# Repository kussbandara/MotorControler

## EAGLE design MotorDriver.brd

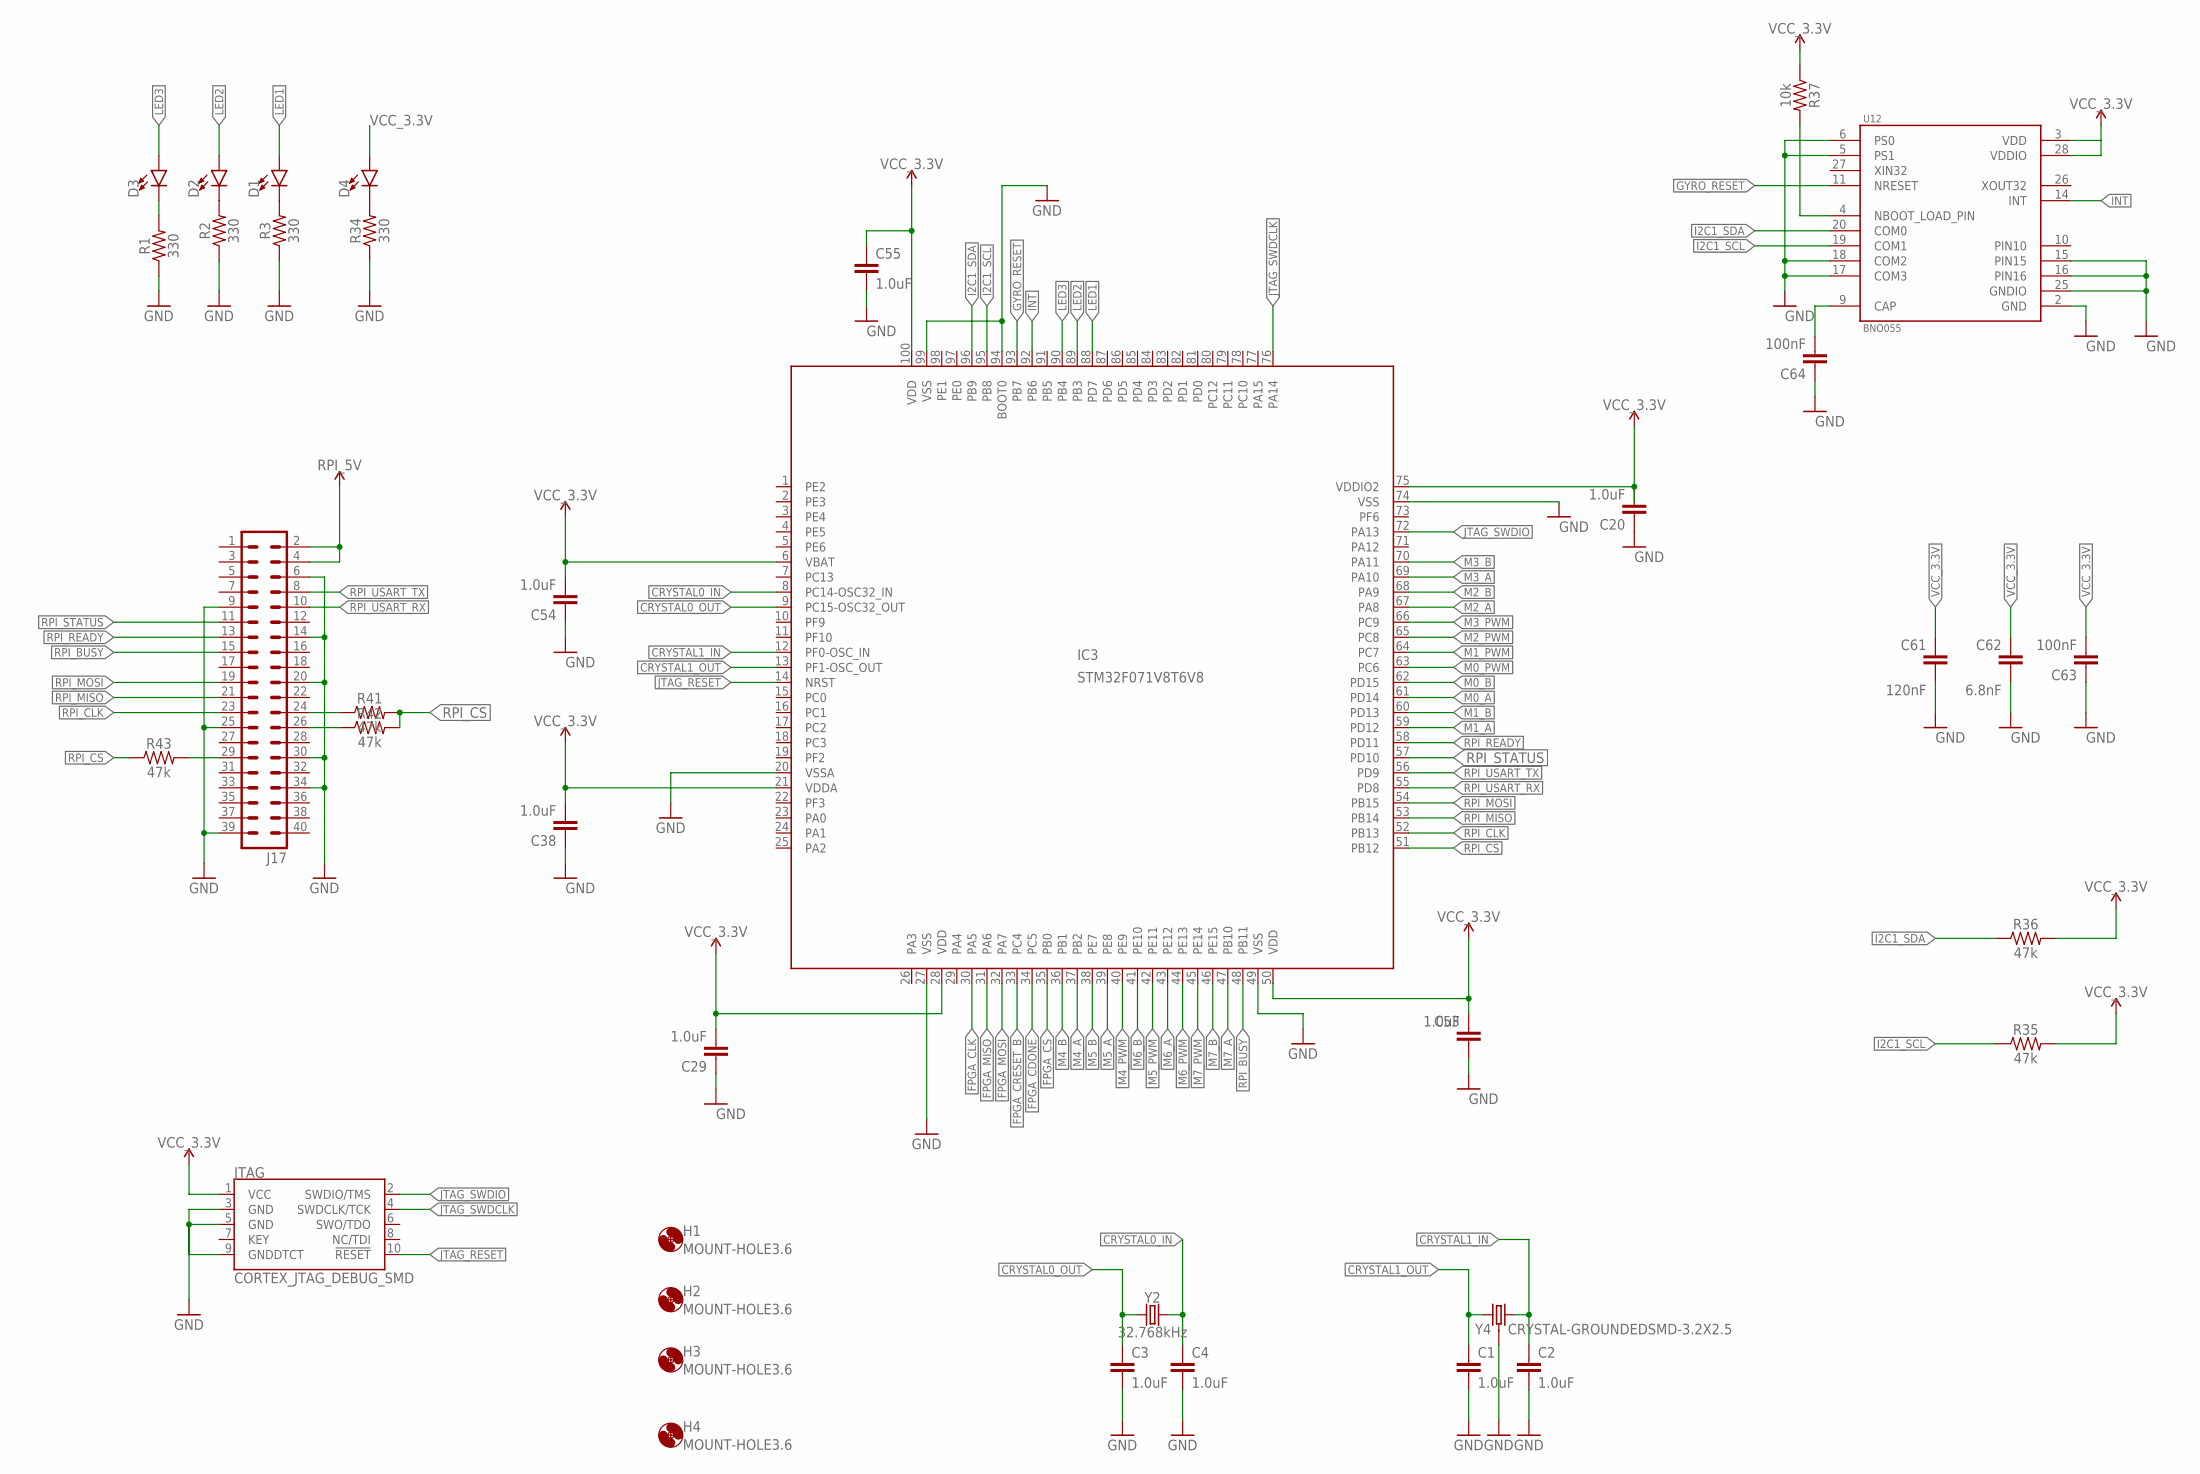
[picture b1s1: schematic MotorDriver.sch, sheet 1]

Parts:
C1, C2, C3, C4, C20, C29, C38, C53, C54, C55: 1.0uF; 0402-TIGHT
C61: 120nF; 0402-TIGHT
C62: 6.8nF; 0402-TIGHT
C63, C64: 100nF; 0402-TIGHT
D1, D2, D3, D4: LED0603; LED-0603
H1, H2, H3, H4: MOUNT-HOLE3.6; 3,6
IC3: STM32F071V8T6V8; LQFP100_14X14
J17: MA20-2
JTAG: CORTEX_JTAG_DEBUG_SMD; 2X5-SMD-1.27MM
R1, R2, R3, R34: 330; 0603
R35, R36, R41, R42, R43: 47k; 0402-TIGHT
R37: 10k; 0402-TIGHT
U12: BNO055; LGA28R50P4X10_380X520X100
Y2: 32.768kHz; CRYSTAL-SMD-3.2X1.5MM
Y4: CRYSTAL-GROUNDEDSMD-3.2X2.5; CRYSTAL-SMD-3.2X2.5MM

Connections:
CRYSTAL0_IN: C4.1, IC3.8 (PC14-OSC32_IN), Y2.P$2 (2)
CRYSTAL0_OUT: C3.1, IC3.9 (PC15-OSC32_OUT), Y2.P$1 (1)
CRYSTAL1_IN: C2.1, IC3.12 (PF0-OSC_IN), Y4.3 (2)
CRYSTAL1_OUT: C1.1, IC3.13 (PF1-OSC_OUT), Y4.1
FPGA_CDONE: IC3.34 (PC5); also elsewhere on the board
FPGA_CLK: IC3.30 (PA5); also elsewhere on the board
FPGA_CRESET_B: IC3.33 (PC4); also elsewhere on the board
FPGA_CS: IC3.35 (PB0); also elsewhere on the board
FPGA_MISO: IC3.31 (PA6); also elsewhere on the board
FPGA_MOSI: IC3.32 (PA7); also elsewhere on the board
GND: C1.2, C2.2, C3.2, C4.2, C20.1, C29.1, C38.1, C53.1, C54.1, C55.2, C61.1, C62.1, C63.1, C64.1, IC3.20 (VSSA), IC3.27 (VSS), IC3.49 (VSS), IC3.74 (VSS), IC3.94 (BOOT0), IC3.99 (VSS), J17.6, J17.9, J17.14, J17.20, J17.25, J17.30, J17.34, J17.39, JTAG.3 (GND), JTAG.5 (GND), JTAG.9 (GNDDTCT), R1.1, R2.1, R3.1, R34.1, U12.2 (GND), U12.5 (PS1), U12.6 (PS0), U12.15 (PIN15), U12.16 (PIN16), U12.17 (COM3), U12.18 (COM2), U12.25 (GNDIO), Y4.2 (3), Y4.4 (3); also elsewhere on the board
GYRO_RESET: IC3.93 (PB7), U12.11 (NRESET)
I2C1_SCL: IC3.95 (PB8), R35.1, U12.19 (COM1)
I2C1_SDA: IC3.96 (PB9), R36.1, U12.20 (COM0)
INT: IC3.92 (PB6), U12.14 (INT)
JTAG_RESET: IC3.14 (NRST), JTAG.10 (!RESET)
JTAG_SWDCLK: IC3.76 (PA14), JTAG.4 (SWDCLK/TCK)
JTAG_SWDIO: IC3.72 (PA13), JTAG.2 (SWDIO/TMS)
LED1: D1.A, IC3.88 (PD7)
LED2: D2.A, IC3.89 (PB3)
LED3: D3.A, IC3.90 (PB4)
M0_A: IC3.61 (PD14); also elsewhere on the board
M0_B: IC3.62 (PD15); also elsewhere on the board
M0_PWM: IC3.63 (PC6); also elsewhere on the board
M1_A: IC3.59 (PD12); also elsewhere on the board
M1_B: IC3.60 (PD13); also elsewhere on the board
M1_PWM: IC3.64 (PC7); also elsewhere on the board
M2_A: IC3.67 (PA8); also elsewhere on the board
M2_B: IC3.68 (PA9); also elsewhere on the board
M2_PWM: IC3.65 (PC8); also elsewhere on the board
M3_A: IC3.69 (PA10); also elsewhere on the board
M3_B: IC3.70 (PA11); also elsewhere on the board
M3_PWM: IC3.66 (PC9); also elsewhere on the board
M4_A: IC3.37 (PB2); also elsewhere on the board
M4_B: IC3.36 (PB1); also elsewhere on the board
M4_PWM: IC3.40 (PE9); also elsewhere on the board
M5_A: IC3.39 (PE8); also elsewhere on the board
M5_B: IC3.38 (PE7); also elsewhere on the board
M5_PWM: IC3.42 (PE11); also elsewhere on the board
M6_A: IC3.43 (PE12); also elsewhere on the board
M6_B: IC3.41 (PE10); also elsewhere on the board
M6_PWM: IC3.44 (PE13); also elsewhere on the board
M7_A: IC3.47 (PB10); also elsewhere on the board
M7_B: IC3.46 (PE15); also elsewhere on the board
M7_PWM: IC3.45 (PE14); also elsewhere on the board
unnamed: D3.C, R1.2
unnamed: D2.C, R2.2
unnamed: D1.C, R3.2
unnamed: D4.C, R34.2
unnamed: R37.2, U12.4 (NBOOT_LOAD_PIN)
unnamed: C64.2, U12.9 (CAP)
unnamed: J17.24, R41.1
unnamed: J17.26, R42.1
unnamed: J17.29, R43.2
PF3: IC3.22 (PF3)
PIN10: U12.10 (PIN10)
RPI_5V: J17.2, J17.4; also elsewhere on the board
RPI_BUSY: IC3.48 (PB11), J17.15
RPI_CLK: IC3.52 (PB13), J17.23
RPI_CS: IC3.51 (PB12), R41.2, R42.2, R43.1
RPI_MISO: IC3.53 (PB14), J17.21
RPI_MOSI: IC3.54 (PB15), J17.19
RPI_READY: IC3.58 (PD11), J17.13
RPI_STATUS: IC3.57 (PD10), J17.11
RPI_USART_RX: IC3.55 (PD8), J17.10
RPI_USART_TX: IC3.56 (PD9), J17.8
VCC_3.3V: C20.2, C29.2, C38.2, C53.2, C54.2, C55.1, C61.2, C62.2, C63.2, D4.A, IC3.6 (VBAT), IC3.21 (VDDA), IC3.28 (VDD), IC3.50 (VDD), IC3.75 (VDDIO2), IC3.100 (VDD), JTAG.1 (VCC), R35.2, R36.2, R37.1, U12.3 (VDD), U12.28 (VDDIO); also elsewhere on the board

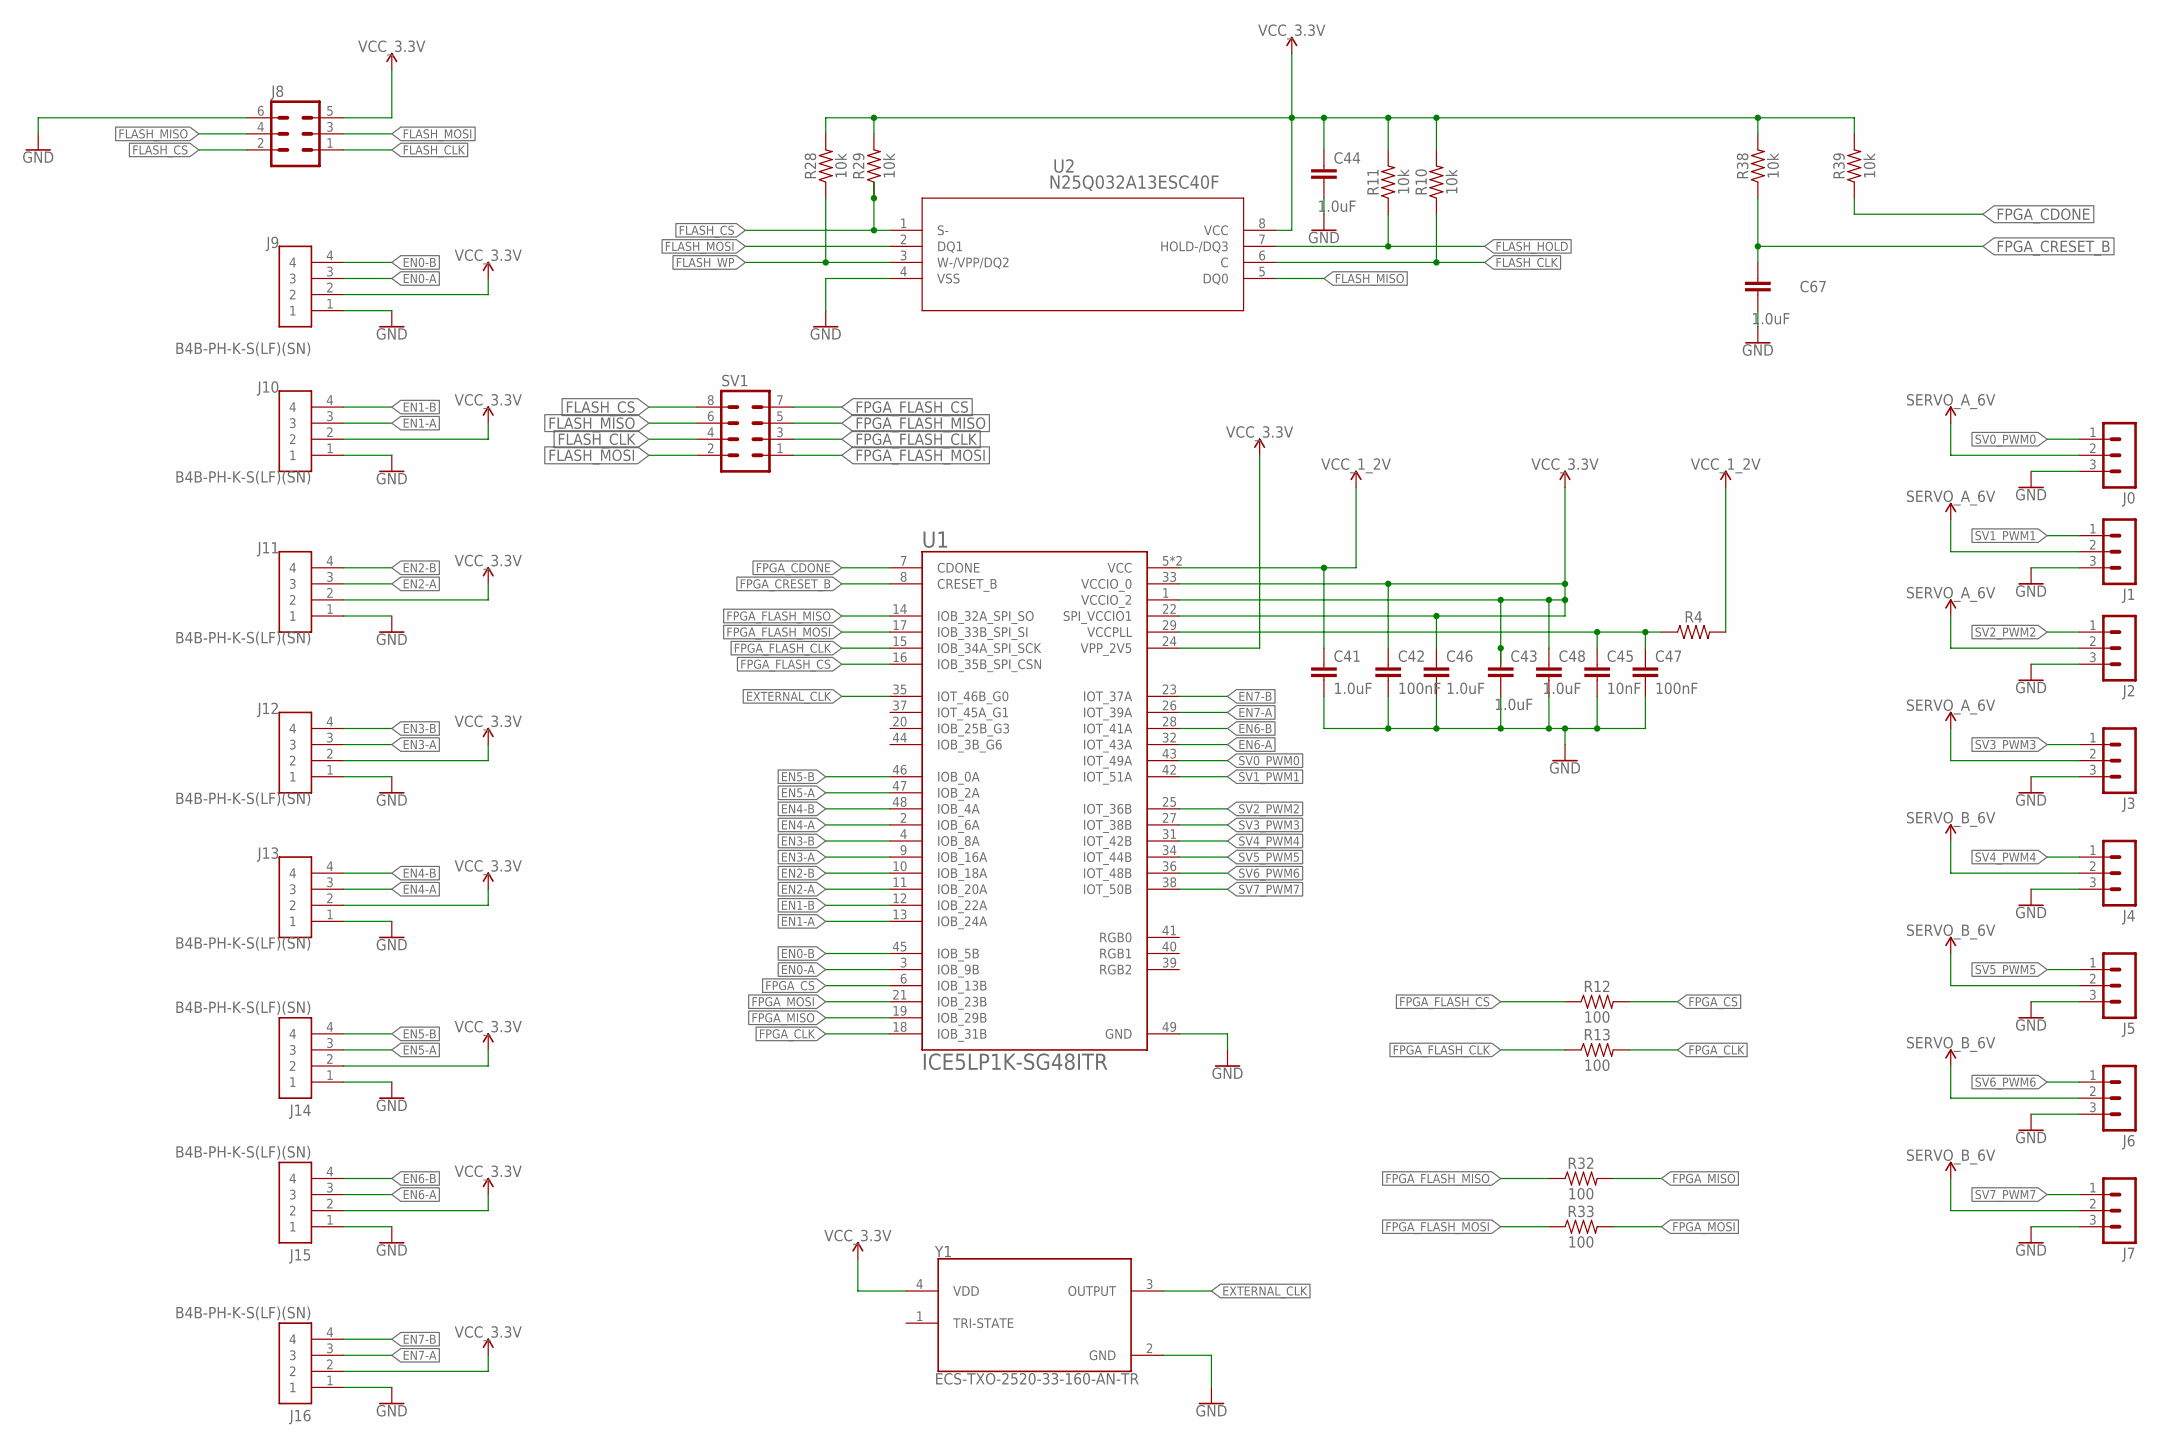
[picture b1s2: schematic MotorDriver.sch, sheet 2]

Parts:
C41, C43, C44, C46, C48, C67: 1.0uF; 0402-TIGHT
C42, C47: 100nF; 0402-TIGHT
C45: 10nF; 0402-TIGHT
J0, J1, J2, J3, J4, J5, J6, J7: MA03-1
J8: MA03-2
J9, J10, J11, J12, J13, J14, J15, J16: B4B-PH-K-S(LF)(SN); JST_B4B-PH-K-S(LF)(SN)
R4: 100; 0402-TIGHT
R10, R11, R28, R29, R38, R39: 10k; 0603
R12, R13, R32, R33: 100; 0603
SV1: MA04-2
U1: ICE5LP1K-SG48ITR; QFN50P700X700X100-49N
U2: N25Q032A13ESC40F; SO8N_5X4_MRN
Y1: ECS-TXO-2520-33-160-AN-TR; OSC_ECS-TXO-2520-33-160-AN-TR

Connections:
EN0-A: J9.3, U1.3 (IOB_9B)
EN0-B: J9.4, U1.45 (IOB_5B)
EN1-A: J10.3, U1.13 (IOB_24A)
EN1-B: J10.4, U1.12 (IOB_22A)
EN2-A: J11.3, U1.11 (IOB_20A)
EN2-B: J11.4, U1.10 (IOB_18A)
EN3-A: J12.3, U1.9 (IOB_16A)
EN3-B: J12.4, U1.4 (IOB_8A)
EN4-A: J13.3, U1.2 (IOB_6A)
EN4-B: J13.4, U1.48 (IOB_4A)
EN5-A: J14.3, U1.47 (IOB_2A)
EN5-B: J14.4, U1.46 (IOB_0A)
EN6-A: J15.3, U1.32 (IOT_43A)
EN6-B: J15.4, U1.28 (IOT_41A)
EN7-A: J16.3, U1.26 (IOT_39A)
EN7-B: J16.4, U1.23 (IOT_37A)
EXTERNAL_CLK: U1.35 (IOT_46B_G0), Y1.3 (OUTPUT)
FLASH_CLK: J8.1, R10.1, SV1.4, U2.6 (C)
FLASH_CS: J8.2, R29.1, SV1.8, U2.1 (S-)
FLASH_HOLD: R11.1, U2.7 (HOLD-/DQ3)
FLASH_MISO: J8.4, SV1.6, U2.5 (DQ0)
FLASH_MOSI: J8.3, SV1.2, U2.2 (DQ1)
FLASH_WP: R28.1, U2.3 (W-/VPP/DQ2)
FPGA_CDONE: R39.1, U1.7 (CDONE); also elsewhere on the board
FPGA_CLK: R13.2, U1.18 (IOB_31B); also elsewhere on the board
FPGA_CRESET_B: C67.1, R38.1, U1.8 (CRESET_B); also elsewhere on the board
FPGA_CS: R12.2, U1.6 (IOB_13B); also elsewhere on the board
FPGA_FLASH_CLK: R13.1, SV1.3, U1.15 (IOB_34A_SPI_SCK)
FPGA_FLASH_CS: R12.1, SV1.7, U1.16 (IOB_35B_SPI_CSN)
FPGA_FLASH_MISO: R32.1, SV1.5, U1.14 (IOB_32A_SPI_SO)
FPGA_FLASH_MOSI: R33.1, SV1.1, U1.17 (IOB_33B_SPI_SI)
FPGA_MISO: R32.2, U1.19 (IOB_29B); also elsewhere on the board
FPGA_MOSI: R33.2, U1.21 (IOB_23B); also elsewhere on the board
GND: C41.2, C42.2, C43.2, C44.2, C45.2, C46.2, C47.2, C48.2, C67.2, J0.3, J1.3, J2.3, J3.3, J4.3, J5.3, J6.3, J7.3, J8.6, J9.1, J10.1, J11.1, J12.1, J13.1, J14.1, J15.1, J16.1, U1.49 (GND), U2.4 (VSS), Y1.2 (GND); also elsewhere on the board
unnamed: C45.1, C47.1, R4.1, U1.29 (VCCPLL)
SERVO_A_6V: J0.2, J1.2, J2.2, J3.2; also elsewhere on the board
SERVO_B_6V: J4.2, J5.2, J6.2, J7.2; also elsewhere on the board
SV0_PWM0: J0.1, U1.43 (IOT_49A)
SV1_PWM1: J1.1, U1.42 (IOT_51A)
SV2_PWM2: J2.1, U1.25 (IOT_36B)
SV3_PWM3: J3.1, U1.27 (IOT_38B)
SV4_PWM4: J4.1, U1.31 (IOT_42B)
SV5_PWM5: J5.1, U1.34 (IOT_44B)
SV6_PWM6: J6.1, U1.36 (IOT_48B)
SV7_PWM7: J7.1, U1.38 (IOT_50B)
VCC_1_2V: C41.1, R4.2, U1.5 (VCC), U1.30 (VCC); also elsewhere on the board
VCC_3.3V: C42.1, C43.1, C44.1, C46.1, C48.1, J8.5, J9.2, J10.2, J11.2, J12.2, J13.2, J14.2, J15.2, J16.2, R10.2, R11.2, R28.2, R29.2, R38.2, R39.2, U1.1 (VCCIO_2), U1.22 (SPI_VCCIO1), U1.24 (VPP_2V5), U1.33 (VCCIO_0), U2.8 (VCC), Y1.4 (VDD); also elsewhere on the board

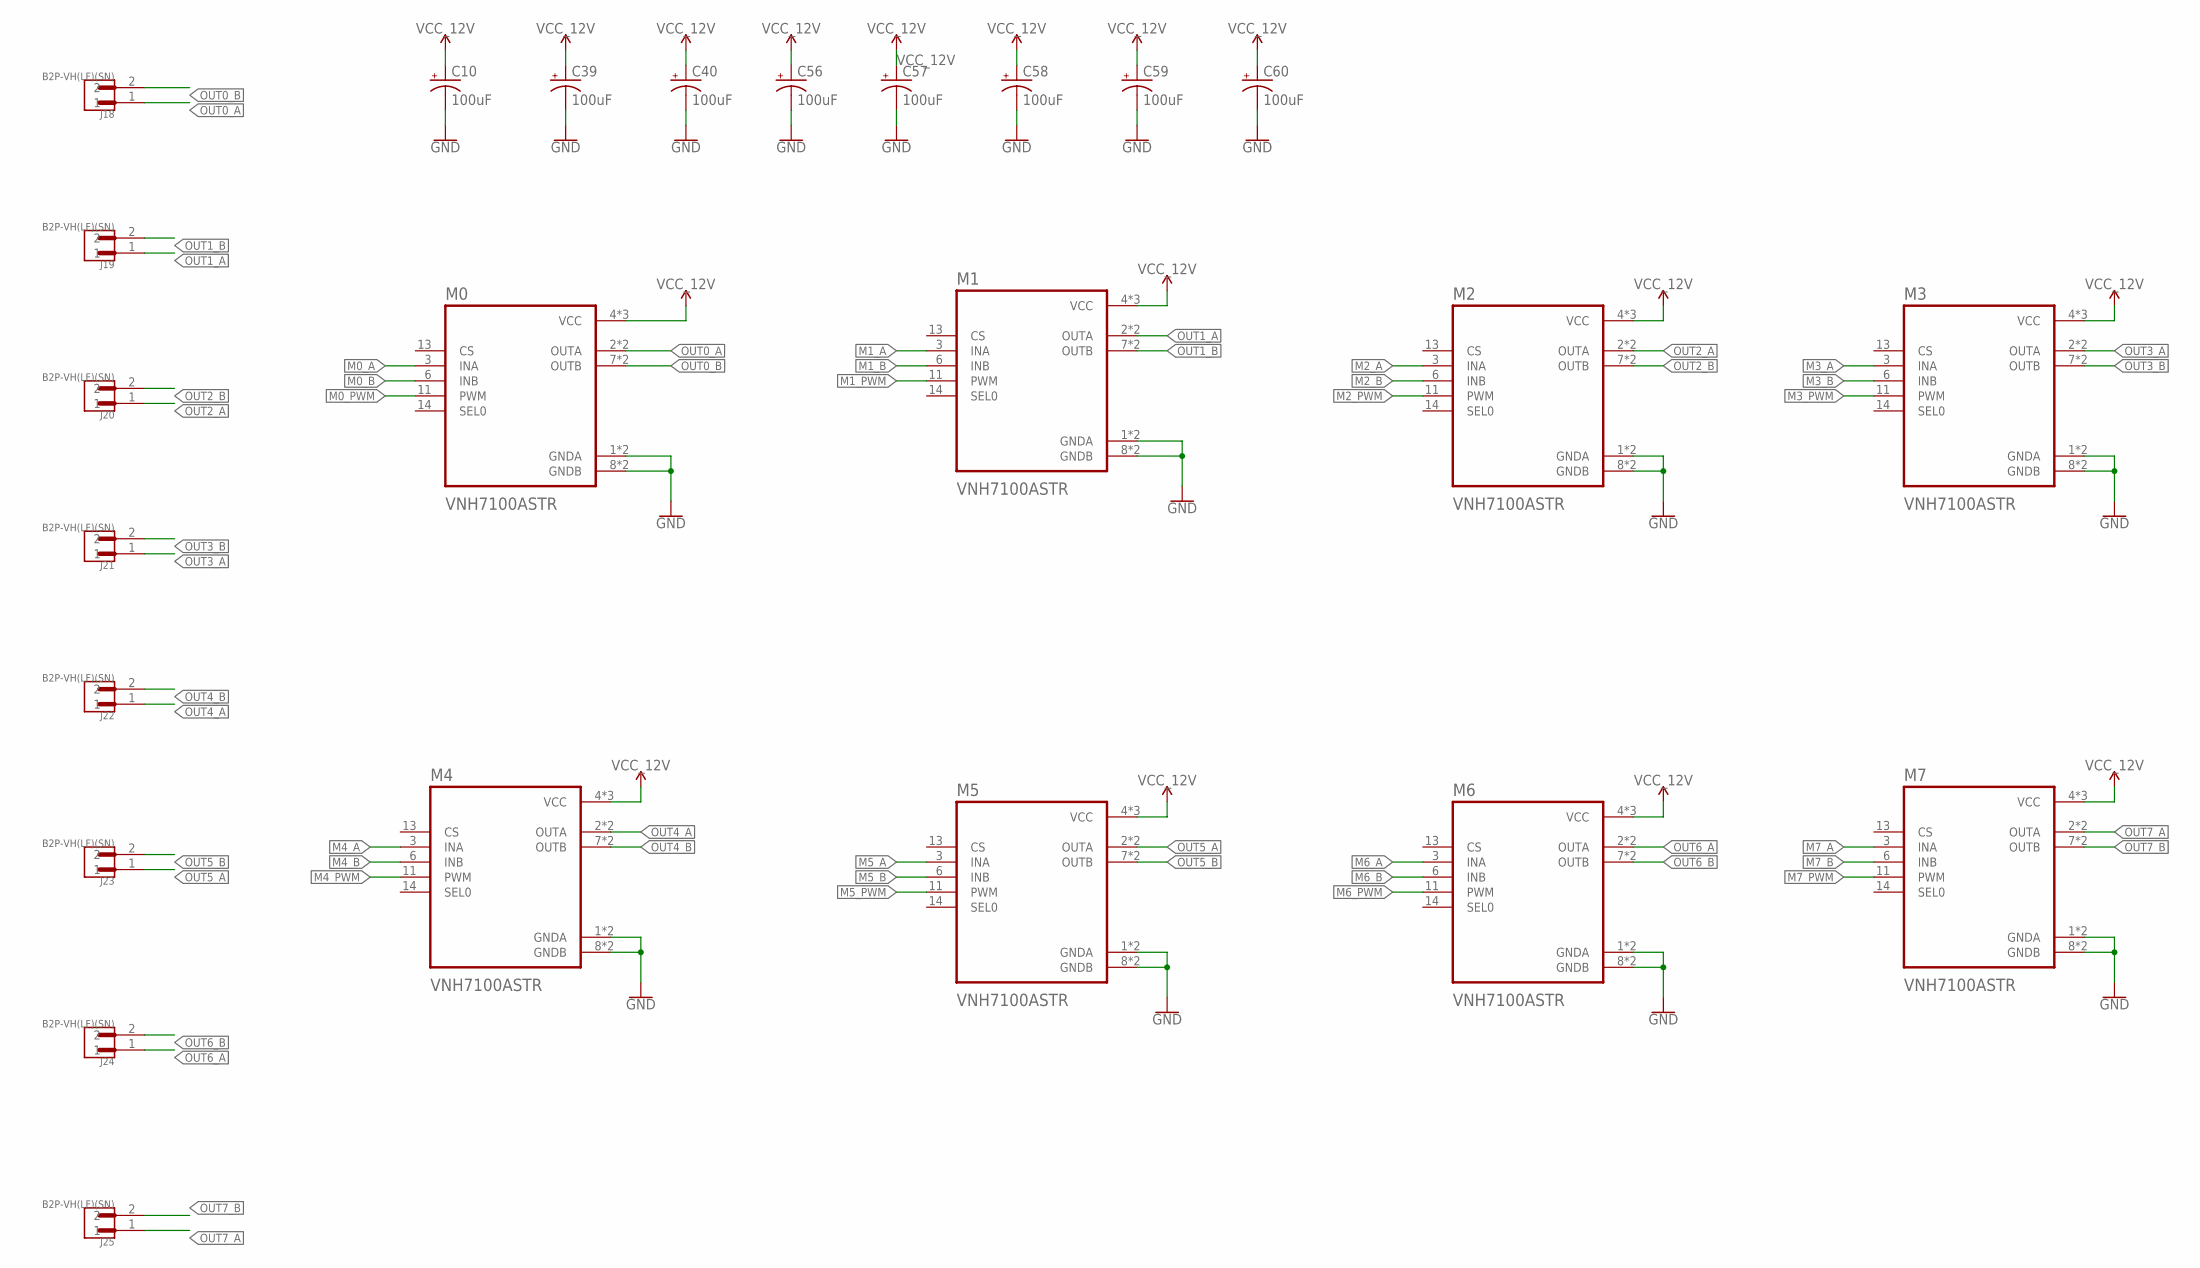
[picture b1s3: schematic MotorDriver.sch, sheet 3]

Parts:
C10, C39, C40, C56, C57, C58, C59, C60: 100uF; PANASONIC_D
J18, J19, J20, J21, J22, J23, J24, J25: B2P-VH(LF)(SN); JST_B2P-VH(LF)(SN)
M0, M1, M2, M3, M4, M5, M6, M7: VNH7100ASTR; SOIC127P600X175-16N

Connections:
GND: C10.-, C39.-, C40.-, C56.-, C57.-, C58.-, C59.-, C60.-, M0.1 (GNDA), M0.8 (GNDB), M0.9 (GNDB), M0.16 (GNDA), M1.1 (GNDA), M1.8 (GNDB), M1.9 (GNDB), M1.16 (GNDA), M2.1 (GNDA), M2.8 (GNDB), M2.9 (GNDB), M2.16 (GNDA), M3.1 (GNDA), M3.8 (GNDB), M3.9 (GNDB), M3.16 (GNDA), M4.1 (GNDA), M4.8 (GNDB), M4.9 (GNDB), M4.16 (GNDA), M5.1 (GNDA), M5.8 (GNDB), M5.9 (GNDB), M5.16 (GNDA), M6.1 (GNDA), M6.8 (GNDB), M6.9 (GNDB), M6.16 (GNDA), M7.1 (GNDA), M7.8 (GNDB), M7.9 (GNDB), M7.16 (GNDA); also elsewhere on the board
M0_A: M0.3 (INA); also elsewhere on the board
M0_B: M0.6 (INB); also elsewhere on the board
M0_PWM: M0.11 (PWM); also elsewhere on the board
M1_A: M1.3 (INA); also elsewhere on the board
M1_B: M1.6 (INB); also elsewhere on the board
M1_PWM: M1.11 (PWM); also elsewhere on the board
M2_A: M2.3 (INA); also elsewhere on the board
M2_B: M2.6 (INB); also elsewhere on the board
M2_PWM: M2.11 (PWM); also elsewhere on the board
M3_A: M3.3 (INA); also elsewhere on the board
M3_B: M3.6 (INB); also elsewhere on the board
M3_PWM: M3.11 (PWM); also elsewhere on the board
M4_A: M4.3 (INA); also elsewhere on the board
M4_B: M4.6 (INB); also elsewhere on the board
M4_PWM: M4.11 (PWM); also elsewhere on the board
M5_A: M5.3 (INA); also elsewhere on the board
M5_B: M5.6 (INB); also elsewhere on the board
M5_PWM: M5.11 (PWM); also elsewhere on the board
M6_A: M6.3 (INA); also elsewhere on the board
M6_B: M6.6 (INB); also elsewhere on the board
M6_PWM: M6.11 (PWM); also elsewhere on the board
M7_A: M7.3 (INA); also elsewhere on the board
M7_B: M7.6 (INB); also elsewhere on the board
M7_PWM: M7.11 (PWM); also elsewhere on the board
OUT0_A: J18.1, M0.2 (OUTA), M0.15 (OUTA)
OUT0_B: J18.2, M0.7 (OUTB), M0.10 (OUTB)
OUT1_A: J19.1, M1.2 (OUTA), M1.15 (OUTA)
OUT1_B: J19.2, M1.7 (OUTB), M1.10 (OUTB)
OUT2_A: J20.1, M2.2 (OUTA), M2.15 (OUTA)
OUT2_B: J20.2, M2.7 (OUTB), M2.10 (OUTB)
OUT3_A: J21.1, M3.2 (OUTA), M3.15 (OUTA)
OUT3_B: J21.2, M3.7 (OUTB), M3.10 (OUTB)
OUT4_A: J22.1, M4.2 (OUTA), M4.15 (OUTA)
OUT4_B: J22.2, M4.7 (OUTB), M4.10 (OUTB)
OUT5_A: J23.1, M5.2 (OUTA), M5.15 (OUTA)
OUT5_B: J23.2, M5.7 (OUTB), M5.10 (OUTB)
OUT6_A: J24.1, M6.2 (OUTA), M6.15 (OUTA)
OUT6_B: J24.2, M6.7 (OUTB), M6.10 (OUTB)
OUT7_A: J25.1, M7.2 (OUTA), M7.15 (OUTA)
OUT7_B: J25.2, M7.7 (OUTB), M7.10 (OUTB)
VCC_12V: C10.+, C39.+, C40.+, C56.+, C57.+, C58.+, C59.+, C60.+, M0.4 (VCC), M0.5 (VCC), M0.12 (VCC), M1.4 (VCC), M1.5 (VCC), M1.12 (VCC), M2.4 (VCC), M2.5 (VCC), M2.12 (VCC), M3.4 (VCC), M3.5 (VCC), M3.12 (VCC), M4.4 (VCC), M4.5 (VCC), M4.12 (VCC), M5.4 (VCC), M5.5 (VCC), M5.12 (VCC), M6.4 (VCC), M6.5 (VCC), M6.12 (VCC), M7.4 (VCC), M7.5 (VCC), M7.12 (VCC); also elsewhere on the board

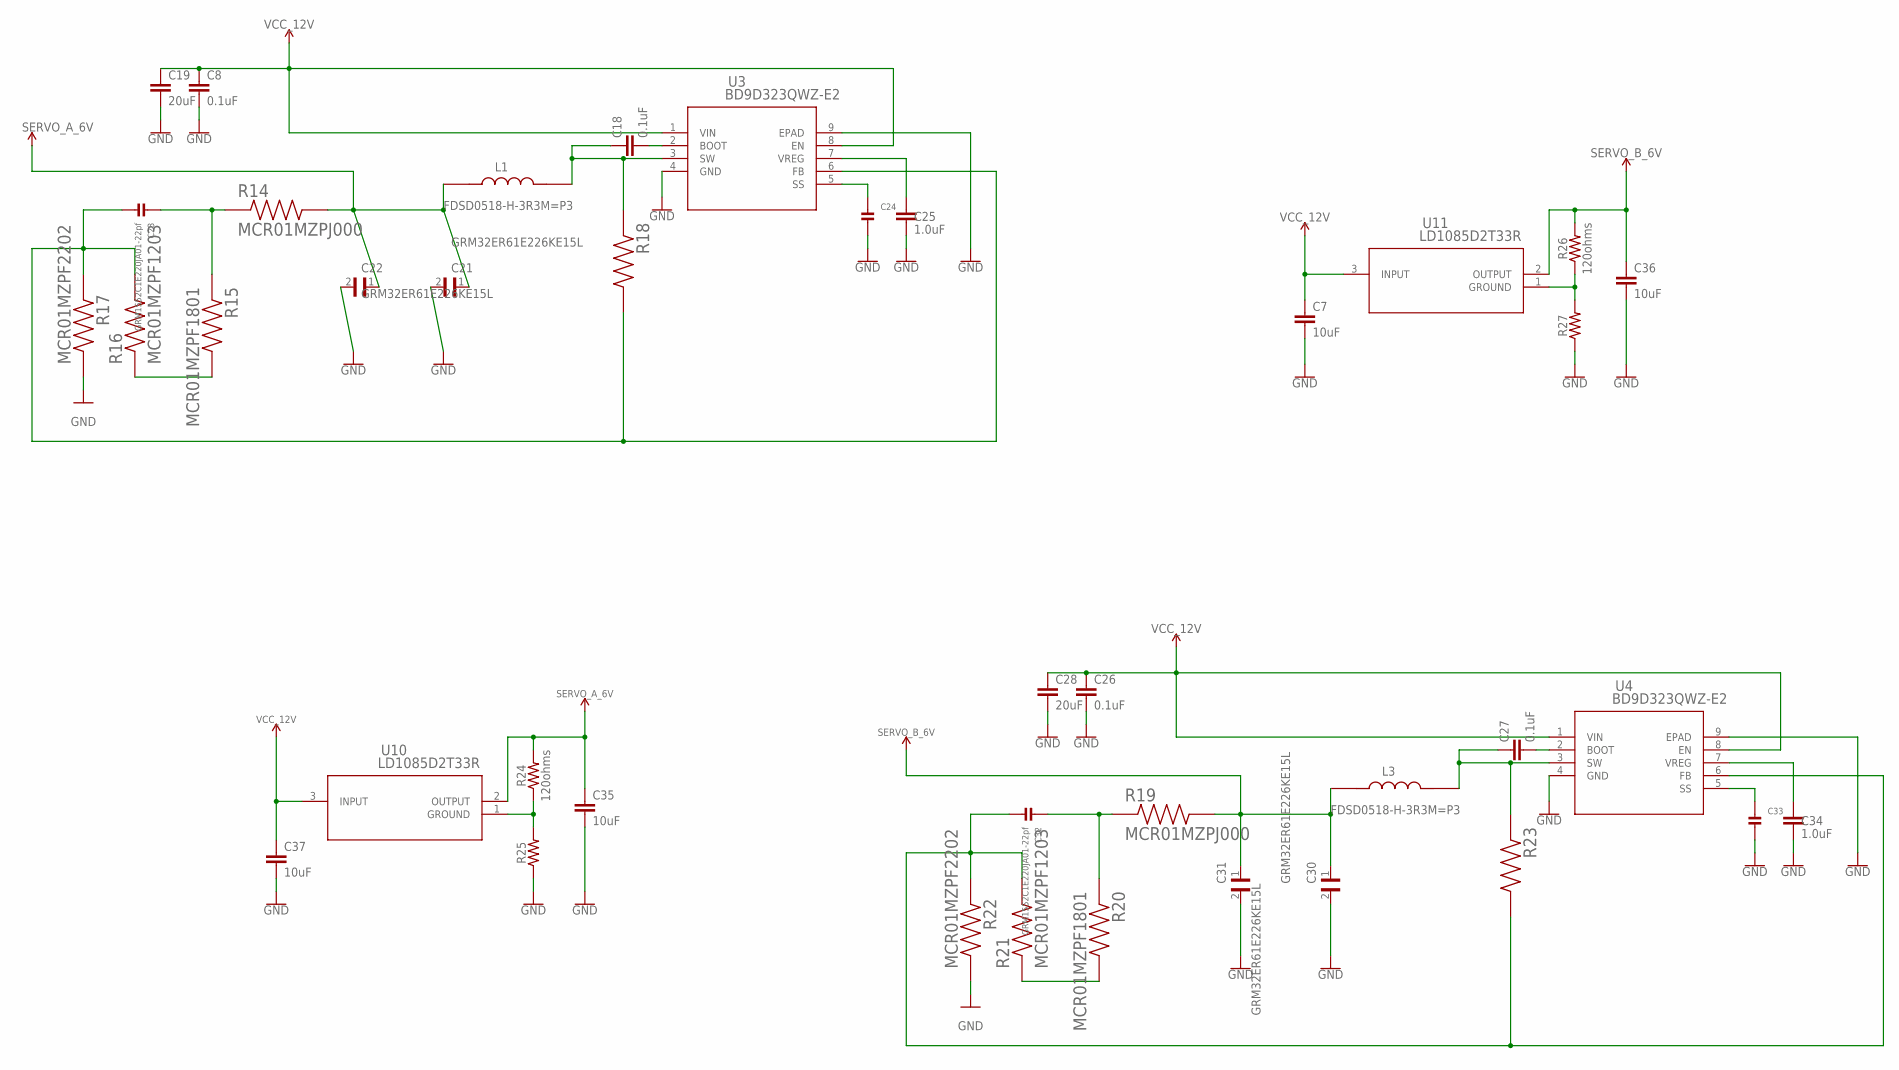
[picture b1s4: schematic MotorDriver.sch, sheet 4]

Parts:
C7, C35, C36, C37: 10uF; 0805
C8, C18, C26, C27: 0.1uF; 0603
C19, C28: 20uF; 1210
C21, C22, C30, C31: GRM32ER61E226KE15L; CAPC3225X270N
C23, C32: GRM1552C1E220JA01-22pf; 0402
C24, C33: GRM155B11H332KA01J-3300pf; 0402
C25, C34: 1.0uF; 0603
L1, L3: FDSD0518-H-3R3M=P3; IND_FDSD0518-H-3R3M=P3
R14, R19: MCR01MZPJ000; RESC1005X40N
R15, R18, R20, R23: MCR01MZPF1801; RESC1005X40N
R16, R21: MCR01MZPF1203; RESC1005X40N
R17, R22: MCR01MZPF2202; RESC1005X40N
R24, R25, R26, R27: 120ohms; 0603
U3, U4: BD9D323QWZ-E2; UMMP008Z2020_ROM
U10, U11: LD1085D2T33R; D2PAK_STM

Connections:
GND: C7.2, C8.2, C19.2, C21.2, C22.2, C24.2, C25.2, C26.2, C28.2, C30.2, C31.2, C33.2, C34.2, C35.2, C36.2, C37.2, R17.1, R22.1, R25.1, R27.1, U3.4 (GND), U3.9 (EPAD), U4.4 (GND), U4.9 (EPAD); also elsewhere on the board
unnamed: C18.2, U3.2 (BOOT)
unnamed: C23.1, R14.1, R15.1
unnamed: R15.2, R16.1
unnamed: C18.1, L1.2, R18.1, U3.3 (SW)
unnamed: C24.1, U3.5 (SS)
unnamed: C25.1, U3.7 (VREG)
unnamed: C23.2, R16.2, R17.2, R18.2, U3.6 (FB)
unnamed: C27.2, U4.2 (BOOT)
unnamed: C32.1, R19.1, R20.1
unnamed: R20.2, R21.1
unnamed: C27.1, L3.2, R23.1, U4.3 (SW)
unnamed: C33.1, U4.5 (SS)
unnamed: C34.1, U4.7 (VREG)
unnamed: C32.2, R21.2, R22.2, R23.2, U4.6 (FB)
unnamed: R24.1, R25.2, U10.1 (GROUND)
unnamed: R26.1, R27.2, U11.1 (GROUND)
SERVO_A_6V: C21.1, C22.1, C35.1, L1.1, R14.2, R24.2, U10.2 (OUTPUT); also elsewhere on the board
SERVO_B_6V: C30.1, C31.1, C36.1, L3.1, R19.2, R26.2, U11.2 (OUTPUT); also elsewhere on the board
VCC_12V: C7.1, C8.1, C19.1, C26.1, C28.1, C37.1, U3.1 (VIN), U3.8 (EN), U4.1 (VIN), U4.8 (EN), U10.3 (INPUT), U11.3 (INPUT); also elsewhere on the board

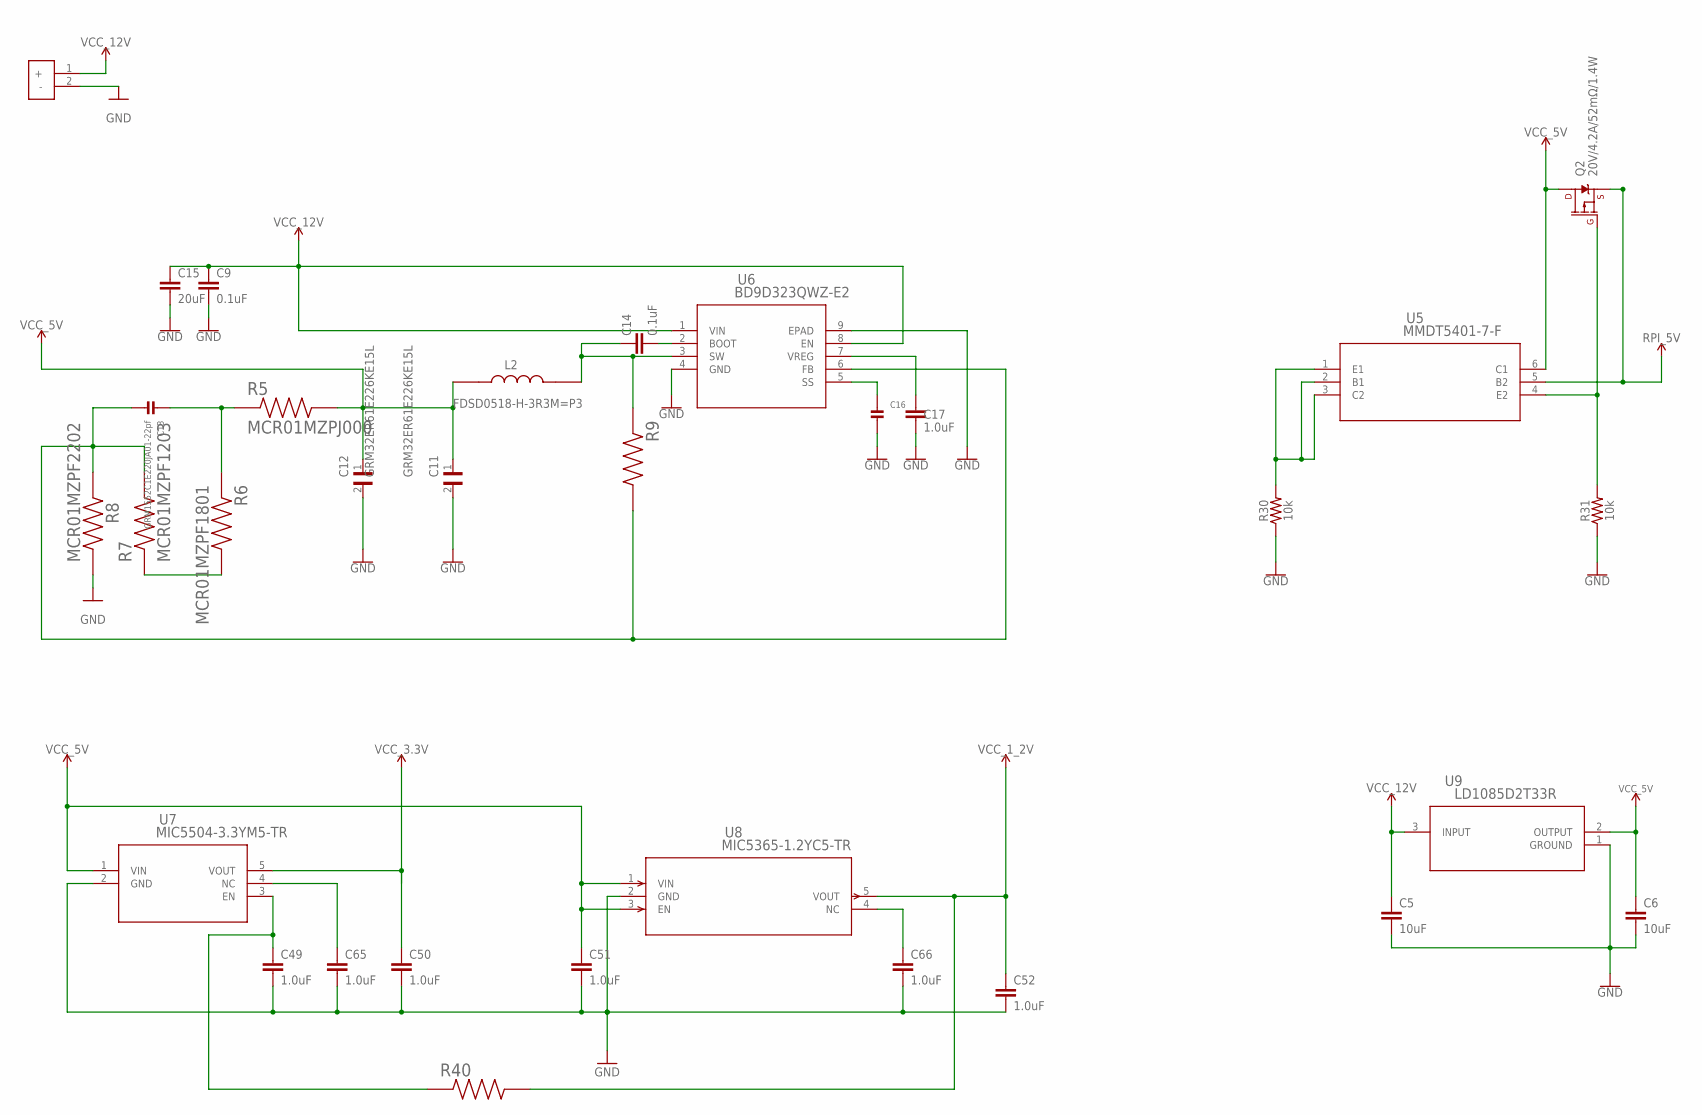
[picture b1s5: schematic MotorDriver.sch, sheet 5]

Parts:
C5, C6: 10uF; 0805
C9, C14: 0.1uF; 0603
C11, C12: GRM32ER61E226KE15L; CAPC3225X270N
C13: GRM1552C1E220JA01-22pf; 0402
C15: 20uF; 1210
C16: GRM155B11H332KA01J-3300pf; 0402
C17, C49, C50, C51, C52, C65, C66: 1.0uF; 0603
J26: XT30PWXT30PW; XT30PW
L2: FDSD0518-H-3R3M=P3; IND_FDSD0518-H-3R3M=P3
Q2: 20V/4.2A/52mΩ/1.4W; SOT23-3
R5: MCR01MZPJ000; RESC1005X40N
R6, R9, R40: MCR01MZPF1801; RESC1005X40N
R7: MCR01MZPF1203; RESC1005X40N
R8: MCR01MZPF2202; RESC1005X40N
R30, R31: 10k; 0603
U5: MMDT5401-7-F; SOT-363_DIO
U6: BD9D323QWZ-E2; UMMP008Z2020_ROM
U7: MIC5504-3.3YM5-TR; SOT-23-5_MC_MCH
U8: MIC5365-1.2YC5-TR; SC-70_C5_MCH
U9: LD1085D2T33R; D2PAK_STM

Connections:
GND: C5.2, C6.2, C9.2, C11.2, C12.2, C15.2, C16.2, C17.2, C49.2, C50.2, C51.2, C52.2, C65.2, C66.2, J26.2 (-), R8.1, R30.1, R31.1, U6.4 (GND), U6.9 (EPAD), U7.2 (GND), U8.2 (GND), U9.1 (GROUND); also elsewhere on the board
unnamed: C14.2, U6.2 (BOOT)
unnamed: C49.1, R40.1, U7.3 (EN)
unnamed: C66.1, U8.4 (NC)
unnamed: C65.1, U7.4 (NC)
unnamed: C16.1, U6.5 (SS)
unnamed: C13.1, R5.1, R6.1
unnamed: R6.2, R7.1
unnamed: C13.2, R7.2, R8.2, R9.2, U6.6 (FB)
unnamed: C17.1, U6.7 (VREG)
unnamed: C14.1, L2.2, R9.1, U6.3 (SW)
unnamed: Q2.1 (G), R31.2, U5.4 (E2)
unnamed: R30.2, U5.1 (E1), U5.2 (B1), U5.3 (C2)
RPI_5V: Q2.2 (S), U5.5 (B2); also elsewhere on the board
VCC_1_2V: C52.1, R40.2, U8.5 (VOUT); also elsewhere on the board
VCC_3.3V: C50.1, U7.5 (VOUT); also elsewhere on the board
VCC_5V: C6.1, C11.1, C12.1, C51.1, L2.1, Q2.3 (D), R5.2, U5.6 (C1), U7.1 (VIN), U8.1 (VIN), U8.3 (EN), U9.2 (OUTPUT)
VCC_12V: C5.1, C9.1, C15.1, J26.1 (+), U6.1 (VIN), U6.8 (EN), U9.3 (INPUT); also elsewhere on the board

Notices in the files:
Core/Src/main.c:
© Copyright (c) 2020 STMicroelectronics.
All rights reserved.
This software component is licensed by ST under BSD 3-Clause license,
the "License"; You may not use this file except in compliance with the
License. You may obtain a copy of the License at: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
(C) COPYRIGHT STMicroelectronics *****END OF FILE
parts and their libraries:
SparkFun-Capacitors: Licensing: Creative Commons ShareAlike 4.0 International - https://creativecommons.org/licenses/by-sa/4.0
COPYRIGHT: Copyright (C) 2018 Accelerated Designs. All rights reserved
